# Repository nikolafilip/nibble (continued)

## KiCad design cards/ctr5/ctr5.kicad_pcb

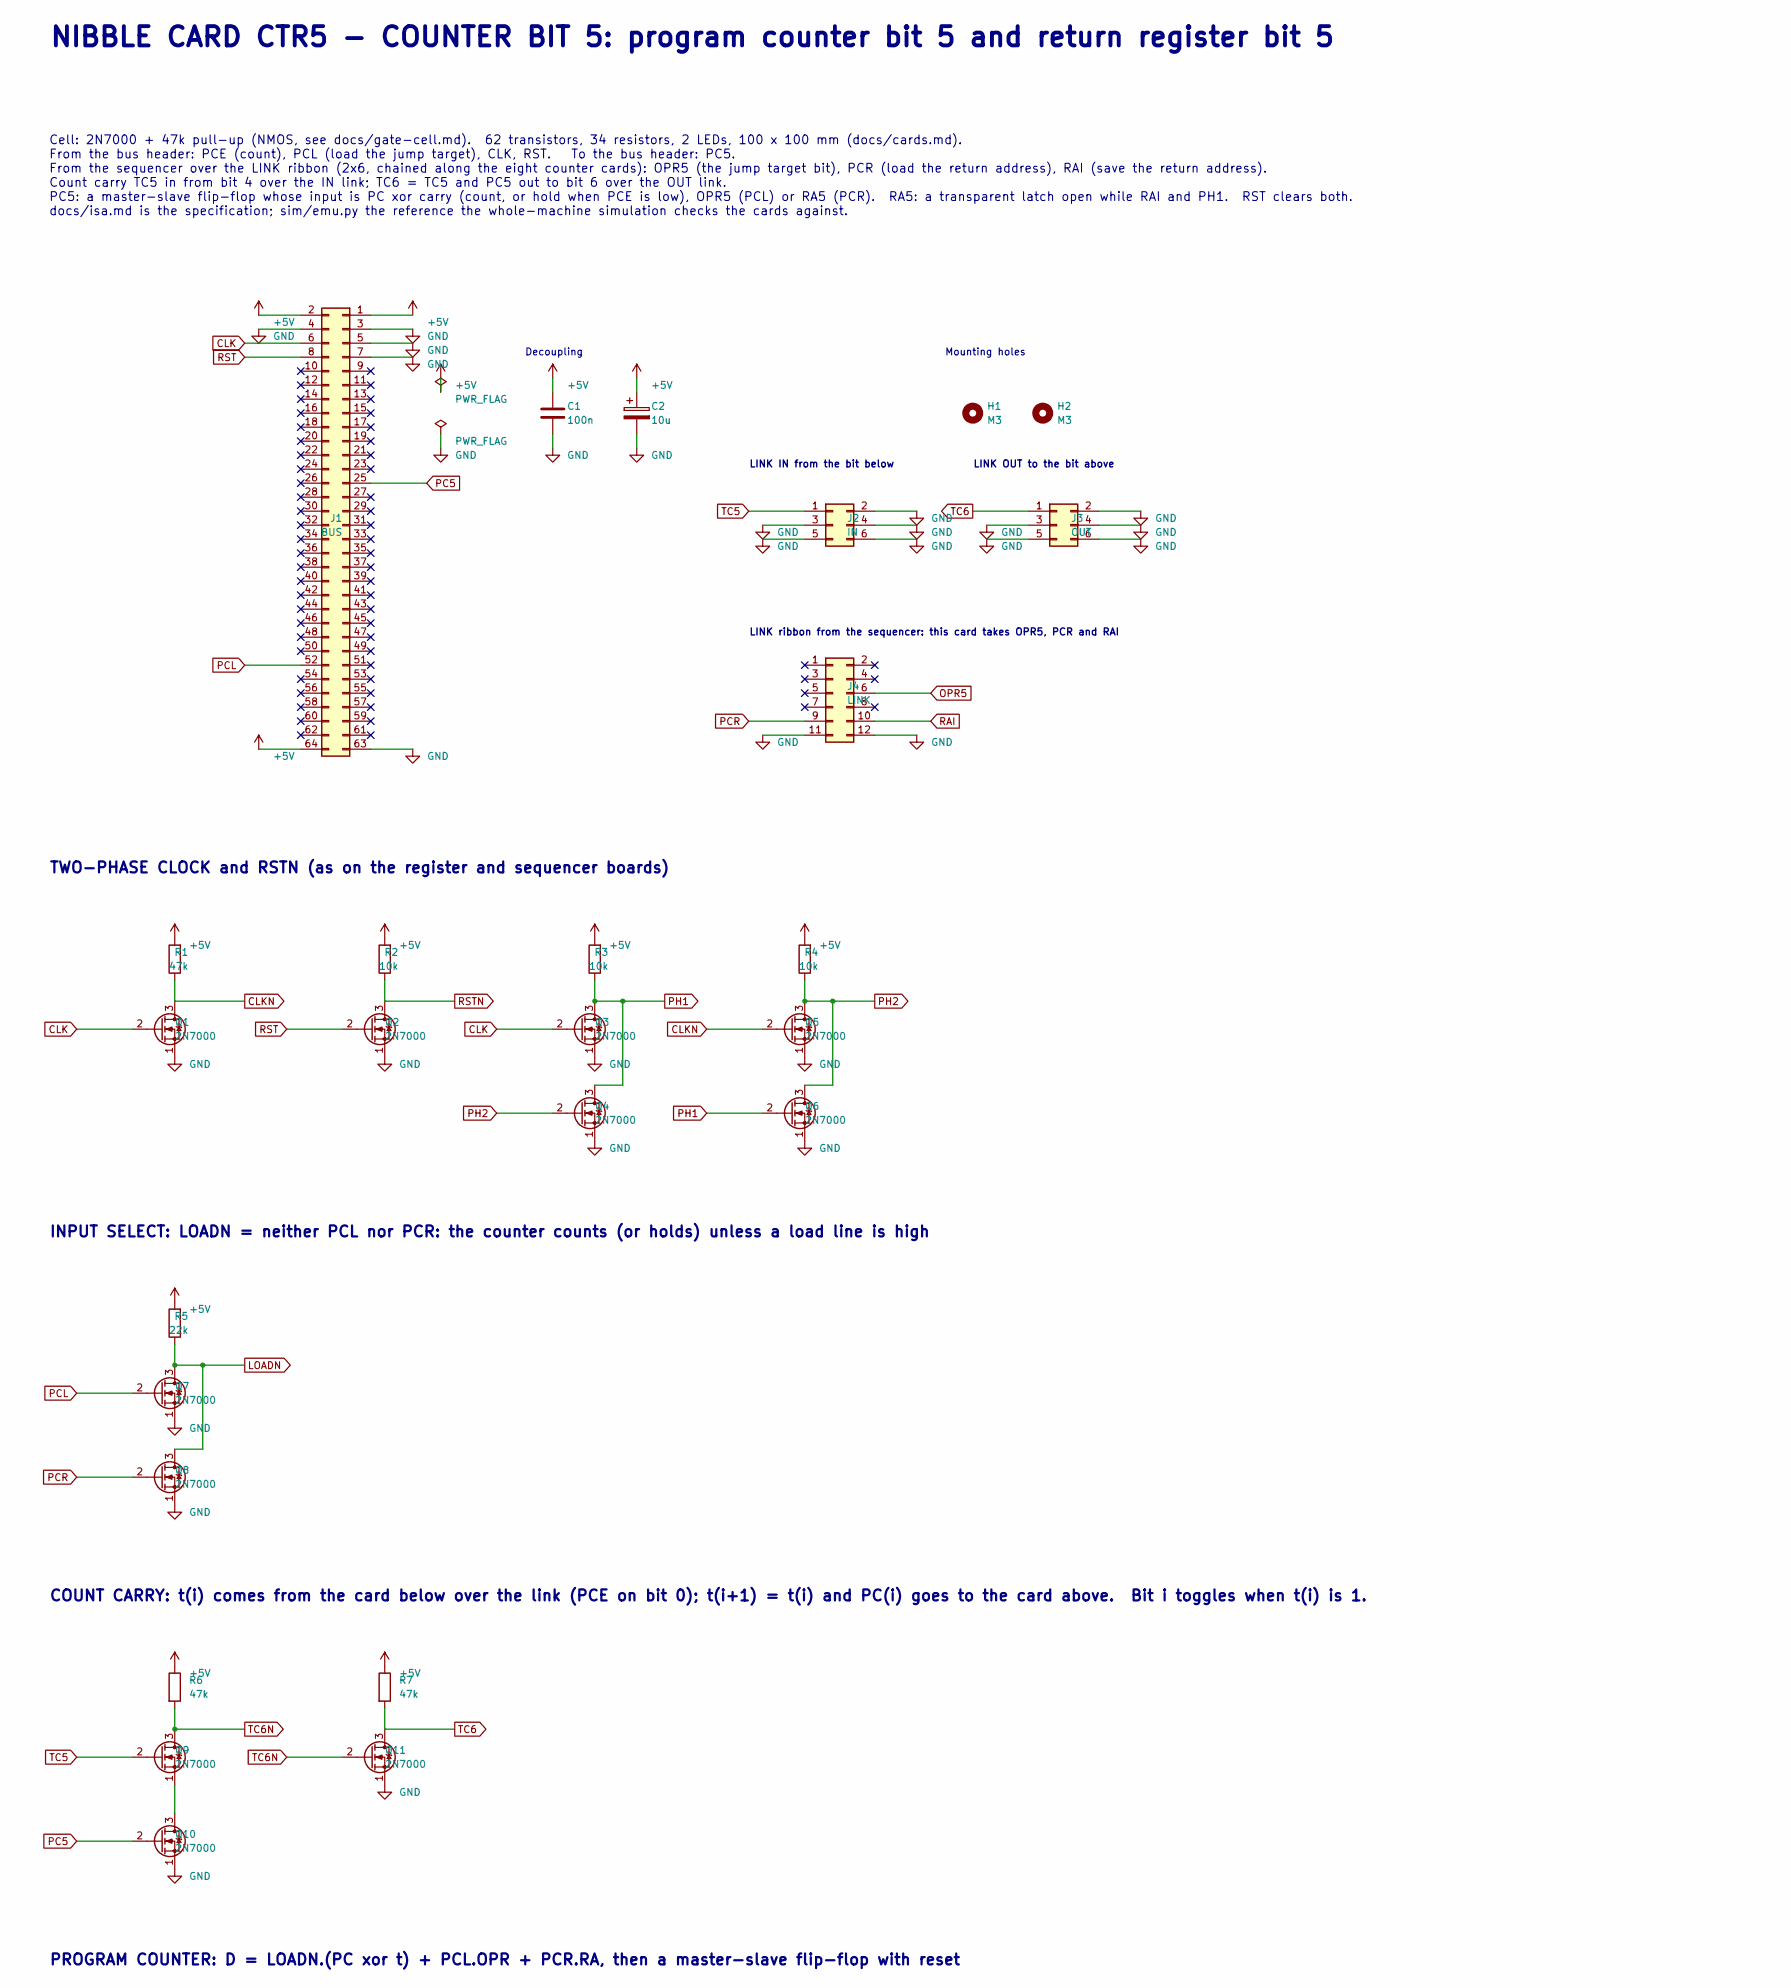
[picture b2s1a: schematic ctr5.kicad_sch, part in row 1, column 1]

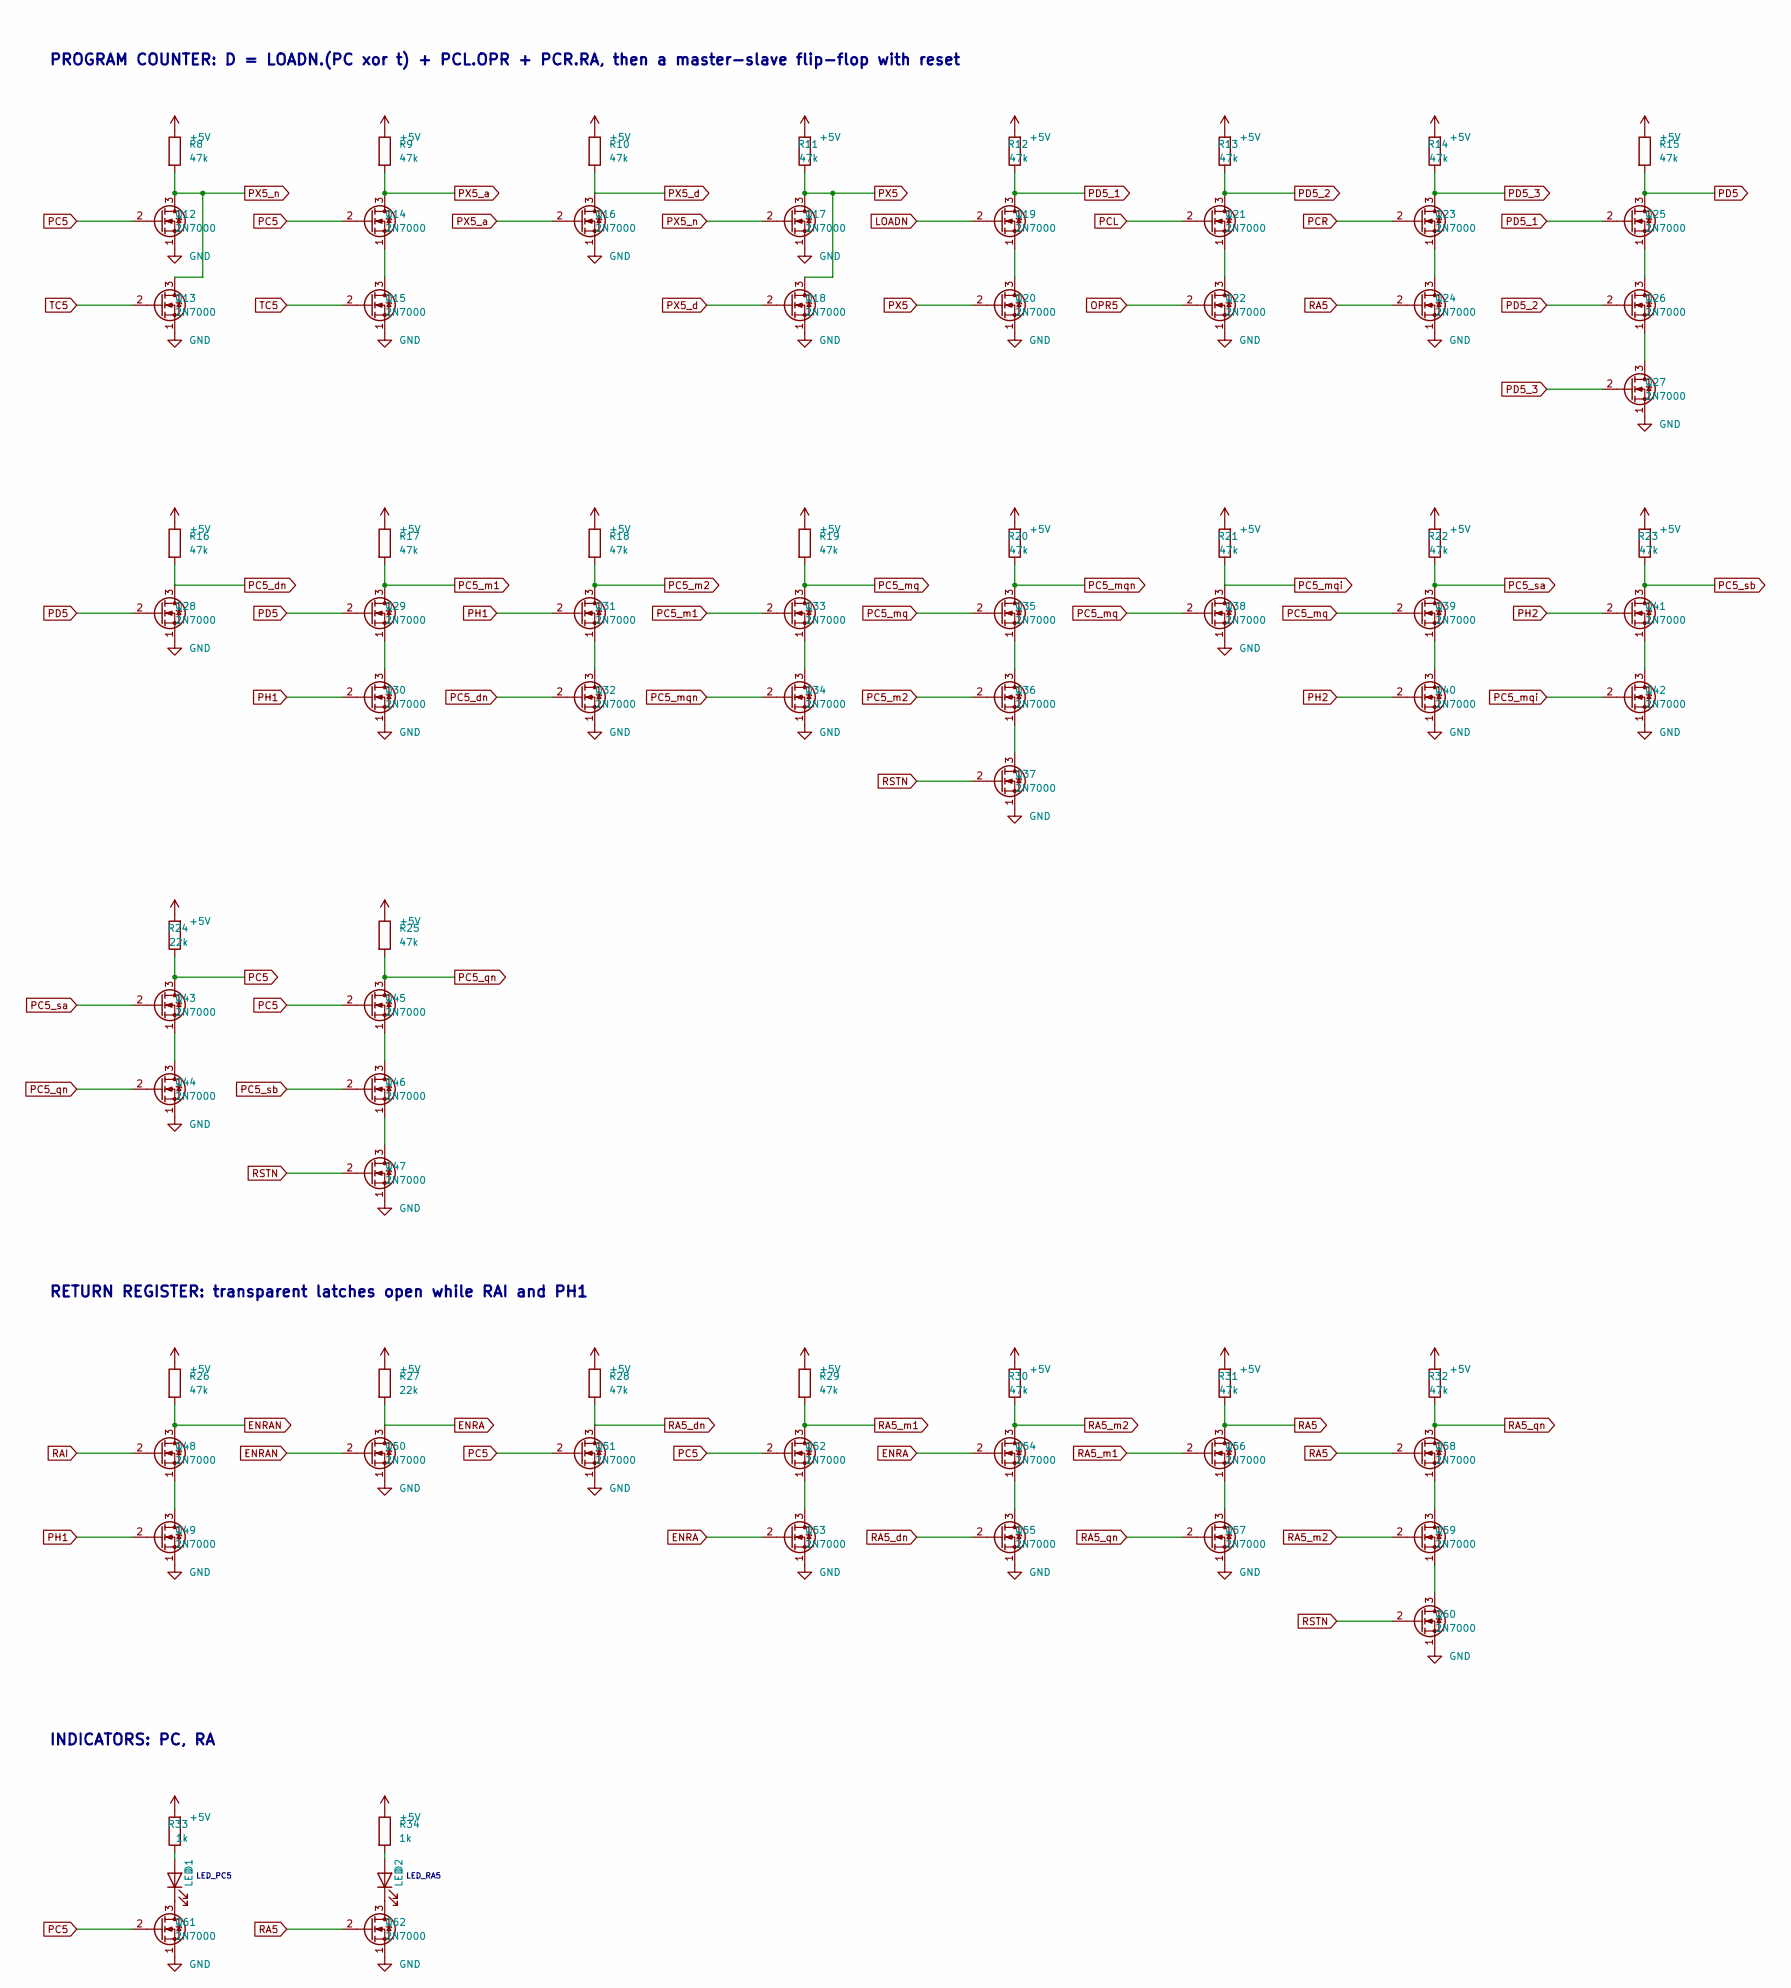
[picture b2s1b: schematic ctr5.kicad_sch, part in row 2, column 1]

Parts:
C1: 100n; C_Disc_D5.0mm_W2.5mm_P2.50mm
C2: 10u; CP_Radial_D5.0mm_P2.00mm
D1, D2: LED; LED_D3.0mm
H1, H2: M3; MountingHole_3.2mm_M3_Pad
J1: BUS; IDC-Header_2x32_P2.54mm_Vertical
J2: IN; IDC-Header_2x03_P2.54mm_Vertical
J3: OUT; IDC-Header_2x03_P2.54mm_Vertical
J4: LINK; IDC-Header_2x06_P2.54mm_Vertical
Q1, Q2, Q3, Q4, Q5, Q6, Q7, Q8, Q9, Q10, Q11, Q12, Q13, Q14, Q15, Q16, Q17, Q18, Q19, Q20, Q21, Q22, Q23, Q24, Q25, Q26, Q27, Q28, Q29, Q30, Q31, Q32, Q33, Q34, Q35, Q36, Q37, Q38, Q39, Q40, Q41, Q42, Q43, Q44, Q45, Q46, Q47, Q48, Q49, Q50, Q51, Q52, Q53, Q54, Q55, Q56, Q57, Q58, Q59, Q60, Q61, Q62: 2N7000; TO-92_Inline_Wide
R1, R6, R7, R8, R9, R10, R11, R12, R13, R14, R15, R16, R17, R18, R19, R20, R21, R22, R23, R25, R26, R28, R29, R30, R31, R32: 47k; R_Axial_DIN0207_L6.3mm_D2.5mm_P5.08mm_Vertical
R2, R3, R4: 10k; R_Axial_DIN0207_L6.3mm_D2.5mm_P5.08mm_Vertical
R5, R24, R27: 22k; R_Axial_DIN0207_L6.3mm_D2.5mm_P5.08mm_Vertical
R33, R34: 1k; R_Axial_DIN0207_L6.3mm_D2.5mm_P5.08mm_Vertical

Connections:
+5V: C1.1, C2.1, J1.1, J1.2, J1.64, R1.2, R2.2, R3.2, R4.2, R5.2, R6.1, R7.1, R8.1, R9.1, R10.1, R11.2, R12.2, R13.2, R14.2, R15.1, R16.1, R17.1, R18.1, R19.1, R20.2, R21.2, R22.2, R23.2, R24.2, R25.1, R26.1, R27.1, R28.1, R29.1, R30.2, R31.2, R32.2, R33.2, R34.1
CLK: J1.6, Q1.2 (G), Q3.2 (G)
CLKN: Q1.3 (D), Q5.2 (G), R1.1
ENRA: Q50.3 (D), Q53.2 (G), Q54.2 (G), R27.2
ENRAN: Q48.3 (D), Q50.2 (G), R26.2
GND: C1.2, C2.2, J1.3, J1.4, J1.5, J1.7, J1.63, J2.2, J2.3, J2.4, J2.5, J2.6, J3.2, J3.3, J3.4, J3.5, J3.6, J4.11, J4.12, Q1.1 (S), Q2.1 (S), Q3.1 (S), Q4.1 (S), Q5.1 (S), Q6.1 (S), Q7.1 (S), Q8.1 (S), Q10.1 (S), Q11.1 (S), Q12.1 (S), Q13.1 (S), Q15.1 (S), Q16.1 (S), Q17.1 (S), Q18.1 (S), Q20.1 (S), Q22.1 (S), Q24.1 (S), Q27.1 (S), Q28.1 (S), Q30.1 (S), Q32.1 (S), Q34.1 (S), Q37.1 (S), Q38.1 (S), Q40.1 (S), Q42.1 (S), Q44.1 (S), Q47.1 (S), Q49.1 (S), Q50.1 (S), Q51.1 (S), Q53.1 (S), Q55.1 (S), Q57.1 (S), Q60.1 (S), Q61.1 (S), Q62.1 (S)
LOADN: Q7.3 (D), Q8.3 (D), Q19.2 (G), R5.1
unnamed: D1.2 (A), R33.1
unnamed: D1.1 (K), Q61.3 (D)
unnamed: D2.2 (A), R34.2
unnamed: D2.1 (K), Q62.3 (D)
unnamed: Q9.1 (S), Q10.3 (D)
unnamed: Q14.1 (S), Q15.3 (D)
unnamed: Q19.1 (S), Q20.3 (D)
unnamed: Q21.1 (S), Q22.3 (D)
unnamed: Q23.1 (S), Q24.3 (D)
unnamed: Q25.1 (S), Q26.3 (D)
unnamed: Q26.1 (S), Q27.3 (D)
unnamed: Q29.1 (S), Q30.3 (D)
unnamed: Q31.1 (S), Q32.3 (D)
unnamed: Q33.1 (S), Q34.3 (D)
unnamed: Q35.1 (S), Q36.3 (D)
unnamed: Q36.1 (S), Q37.3 (D)
unnamed: Q39.1 (S), Q40.3 (D)
unnamed: Q41.1 (S), Q42.3 (D)
unnamed: Q43.1 (S), Q44.3 (D)
unnamed: Q45.1 (S), Q46.3 (D)
unnamed: Q46.1 (S), Q47.3 (D)
unnamed: Q48.1 (S), Q49.3 (D)
unnamed: Q52.1 (S), Q53.3 (D)
unnamed: Q54.1 (S), Q55.3 (D)
unnamed: Q56.1 (S), Q57.3 (D)
unnamed: Q58.1 (S), Q59.3 (D)
unnamed: Q59.1 (S), Q60.3 (D)
OPR5: J4.6, Q22.2 (G)
PC5: J1.25, Q10.2 (G), Q12.2 (G), Q14.2 (G), Q43.3 (D), Q45.2 (G), Q51.2 (G), Q52.2 (G), Q61.2 (G), R24.1
PC5_dn: Q28.3 (D), Q32.2 (G), R16.2
PC5_m1: Q29.3 (D), Q33.2 (G), R17.2
PC5_m2: Q31.3 (D), Q36.2 (G), R18.2
PC5_mq: Q33.3 (D), Q35.2 (G), Q38.2 (G), Q39.2 (G), R19.2
PC5_mqi: Q38.3 (D), Q42.2 (G), R21.1
PC5_mqn: Q34.2 (G), Q35.3 (D), R20.1
PC5_qn: Q44.2 (G), Q45.3 (D), R25.2
PC5_sa: Q39.3 (D), Q43.2 (G), R22.1
PC5_sb: Q41.3 (D), Q46.2 (G), R23.1
PCL: J1.52, Q7.2 (G), Q21.2 (G)
PCR: J4.9, Q8.2 (G), Q23.2 (G)
PD5: Q25.3 (D), Q28.2 (G), Q29.2 (G), R15.2
PD5_1: Q19.3 (D), Q25.2 (G), R12.1
PD5_2: Q21.3 (D), Q26.2 (G), R13.1
PD5_3: Q23.3 (D), Q27.2 (G), R14.1
PH1: Q3.3 (D), Q4.3 (D), Q6.2 (G), Q30.2 (G), Q31.2 (G), Q49.2 (G), R3.1
PH2: Q4.2 (G), Q5.3 (D), Q6.3 (D), Q40.2 (G), Q41.2 (G), R4.1
PX5: Q17.3 (D), Q18.3 (D), Q20.2 (G), R11.1
PX5_a: Q14.3 (D), Q16.2 (G), R9.2
PX5_d: Q16.3 (D), Q18.2 (G), R10.2
PX5_n: Q12.3 (D), Q13.3 (D), Q17.2 (G), R8.2
RA5: Q24.2 (G), Q56.3 (D), Q58.2 (G), Q62.2 (G), R31.1
RA5_dn: Q51.3 (D), Q55.2 (G), R28.2
RA5_m1: Q52.3 (D), Q56.2 (G), R29.2
RA5_m2: Q54.3 (D), Q59.2 (G), R30.1
RA5_qn: Q57.2 (G), Q58.3 (D), R32.1
RAI: J4.10, Q48.2 (G)
RST: J1.8, Q2.2 (G)
RSTN: Q2.3 (D), Q37.2 (G), Q47.2 (G), Q60.2 (G), R2.1
TC5: J2.1, Q9.2 (G), Q13.2 (G), Q15.2 (G)
TC6: J3.1, Q11.3 (D), R7.2
TC6N: Q9.3 (D), Q11.2 (G), R6.2

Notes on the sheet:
NIBBLE CARD CTR5 - COUNTER BIT 5: program counter bit 5 and return register bit 5
Cell: 2N7000 + 47k pull-up (NMOS, see docs/gate-cell.md). 62 transistors, 34 resistors, 2 LEDs, 100 x 100 mm (docs/cards.md). From the bus header: PCE (count), PCL (load the jump target), CLK, RST. To the bus header: PC5. From the sequencer over the LINK ribbon (2x6, chained along the eight counter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
TWO-PHASE CLOCK and RSTN (as on the register and sequencer boards)
INPUT SELECT: LOADN = neither PCL nor PCR: the counter counts (or holds) unless a load line is high
COUNT CARRY: t(i) comes from the card below over the link (PCE on bit 0); t(i+1) = t(i) and PC(i) goes to the card above. Bit i toggles when t(i) is 1.
PROGRAM COUNTER: D = LOADN.(PC xor t) + PCL.OPR + PCR.RA, then a master-slave flip-flop with reset
RETURN REGISTER: transparent latches open while RAI and PH1
INDICATORS: PC, RA
LED_PC5
LED_RA5
Decoupling
Mounting holes
LINK IN from the bit below
LINK OUT to the bit above
LINK ribbon from the sequencer: this card takes OPR5, PCR and RAI

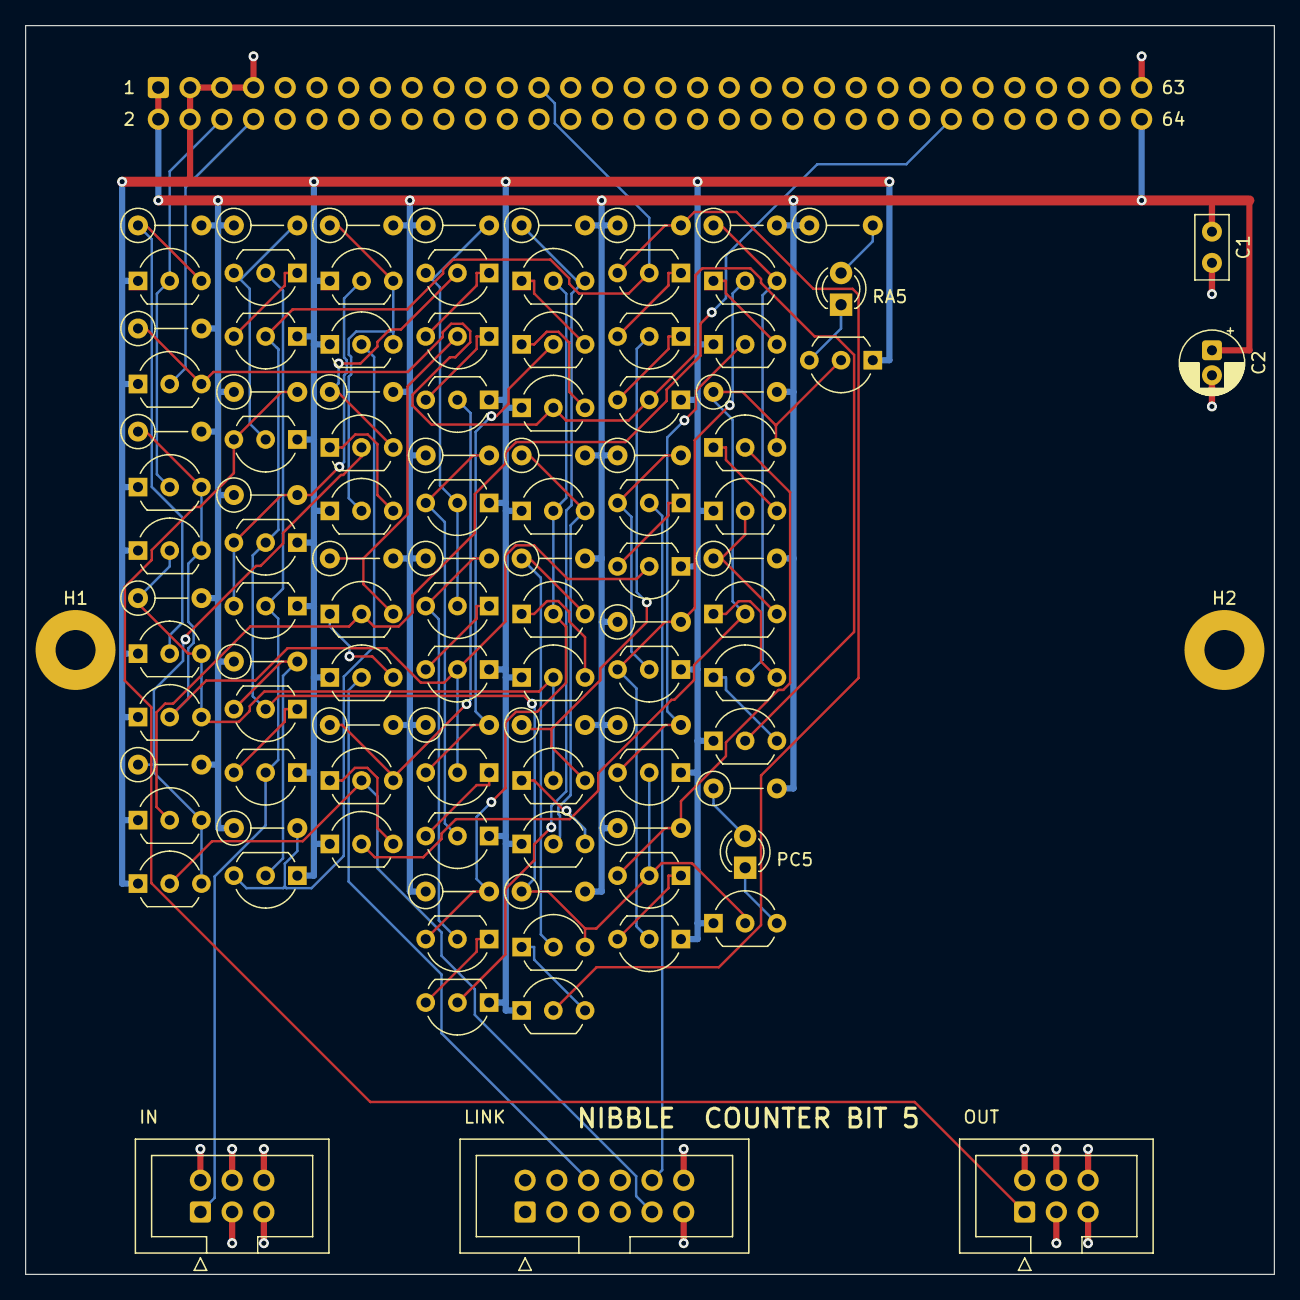
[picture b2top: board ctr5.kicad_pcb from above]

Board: 2 copper layers, 100.0 x 100.0 mm, 106 parts (1 on the bottom side), 68 nets.

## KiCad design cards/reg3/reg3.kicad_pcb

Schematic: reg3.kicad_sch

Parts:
C1: 100n; C_Disc_D5.0mm_W2.5mm_P2.50mm
C2: 10u; CP_Radial_D5.0mm_P2.00mm
D1, D2, D3: LED; LED_D3.0mm
H1, H2: M3; MountingHole_3.2mm_M3_Pad
J1: BUS; IDC-Header_2x32_P2.54mm_Vertical
Q1, Q2, Q3, Q4, Q5, Q6, Q7, Q8, Q9, Q10, Q11, Q12, Q13, Q14, Q15, Q16, Q17, Q18, Q19, Q20, Q21, Q22, Q23, Q24, Q25, Q26, Q27, Q28, Q29, Q30, Q31, Q32, Q33, Q34, Q35, Q36, Q37, Q38, Q39, Q40, Q41, Q42, Q43, Q44, Q45, Q46, Q47, Q48, Q49, Q50, Q51, Q52, Q53, Q54, Q55, Q56, Q57, Q58, Q59, Q60, Q61, Q62, Q63, Q64, Q65, Q66, Q67, Q68, Q69, Q70, Q71, Q72, Q73, Q74, Q75, Q76, Q77, Q78, Q79, Q80, Q81, Q82, Q83, Q84, Q85, Q86, Q87, Q88, Q89, Q90, Q91, Q92, Q93, Q94, Q95, Q96, Q97, Q98, Q99: 2N7000; TO-92_Inline_Wide
R1, R4, R5, R6, R7, R8, R9, R10, R11, R12, R13, R14, R15, R16, R17, R19, R20, R21, R22, R23, R24, R25, R26, R27, R28, R29, R30, R31, R32, R34, R35, R36, R37, R38, R39, R40, R41, R42, R43, R44, R45, R46, R47, R48, R49, R50, R51: 47k; R_Axial_DIN0207_L6.3mm_D2.5mm_P5.08mm_Vertical
R2, R3: 10k; R_Axial_DIN0207_L6.3mm_D2.5mm_P5.08mm_Vertical
R18, R33: 22k; R_Axial_DIN0207_L6.3mm_D2.5mm_P5.08mm_Vertical
R52, R53, R54: 1k; R_Axial_DIN0207_L6.3mm_D2.5mm_P5.08mm_Vertical

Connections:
+5V: C1.1, C2.1, J1.1, J1.2, J1.64, R1.2, R2.2, R3.2, R4.2, R5.2, R6.2, R7.1, R8.1, R9.1, R10.1, R11.1, R12.1, R13.2, R14.2, R15.2, R16.2, R17.2, R18.2, R19.1, R20.1, R21.1, R22.1, R23.1, R24.2, R25.2, R26.2, R27.2, R28.2, R29.2, R30.1, R31.1, R32.1, R33.1, R34.1, R35.1, R36.2, R37.2, R38.2, R39.2, R40.2, R41.2, R42.1, R43.1, R44.1, R45.1, R46.1, R47.1, R48.2, R49.2, R50.2, R51.2, R52.2, R53.1, R54.1
A3: J1.15, Q14.2 (G), Q32.3 (D), Q34.2 (G), Q41.2 (G), Q91.2 (G), Q98.2 (G), R18.1
A3_dn: Q18.3 (D), Q22.2 (G), R10.2
A3_m1: Q19.3 (D), Q23.2 (G), R11.2
A3_m2: Q21.3 (D), Q26.2 (G), R12.2
A3_mq: Q23.3 (D), Q25.2 (G), Q27.2 (G), Q28.2 (G), R13.1
A3_mqi: Q27.3 (D), Q31.2 (G), R15.1
A3_mqn: Q24.2 (G), Q25.3 (D), R14.1
A3_qn: Q33.2 (G), Q34.3 (D), R19.2
A3_sa: Q28.3 (D), Q32.2 (G), R16.1
A3_sb: Q30.3 (D), Q35.2 (G), R17.1
AB: J1.45, Q8.2 (G), Q11.2 (G)
AI: J1.42, Q7.2 (G), Q9.2 (G)
AO: J1.41, Q90.2 (G)
AON3: Q90.3 (D), Q94.2 (G), R49.1
B3: J1.19, Q12.2 (G), Q43.2 (G), Q61.3 (D), Q63.2 (G), Q93.2 (G), Q99.2 (G), R33.2
B3_dn: Q47.3 (D), Q51.2 (G), R25.1
B3_m1: Q48.3 (D), Q52.2 (G), R26.1
B3_m2: Q50.3 (D), Q55.2 (G), R27.1
B3_mq: Q52.3 (D), Q54.2 (G), Q56.2 (G), Q57.2 (G), R28.1
B3_mqi: Q56.3 (D), Q60.2 (G), R30.2
B3_mqn: Q53.2 (G), Q54.3 (D), R29.1
B3_qn: Q62.2 (G), Q63.3 (D), R34.2
B3_sa: Q57.3 (D), Q61.2 (G), R31.2
B3_sb: Q59.3 (D), Q64.2 (G), R32.2
BA: J1.46, Q37.2 (G), Q40.2 (G)
BD3: Q94.3 (D), Q96.2 (G), R51.1
BI: J1.44, Q36.2 (G), Q38.2 (G)
BO: J1.43, Q92.2 (G)
BON3: Q92.3 (D), Q95.2 (G), R50.1
BUS3#: J1.11, Q6.2 (G), Q96.3 (D)
CLK: J1.6, Q1.2 (G), Q2.2 (G)
CLKN: Q1.3 (D), Q4.2 (G), R1.1
D3: Q6.3 (D), Q10.2 (G), Q39.2 (G), Q67.2 (G), R4.1
DA3: Q15.3 (D), Q18.2 (G), Q19.2 (G), R9.2
DA3_1: Q9.3 (D), Q15.2 (G), R6.1
DA3_2: Q11.3 (D), Q16.2 (G), R7.2
DA3_3: Q13.3 (D), Q17.2 (G), R8.2
DB3: Q44.3 (D), Q47.2 (G), Q48.2 (G), R24.1
DB3_1: Q38.3 (D), Q44.2 (G), R21.2
DB3_2: Q40.3 (D), Q45.2 (G), R22.2
DB3_3: Q42.3 (D), Q46.2 (G), R23.2
DO3: Q70.3 (D), Q72.2 (G), Q73.2 (G), R38.1
DO3_1: Q66.3 (D), Q70.2 (G), R36.1
DO3_2: Q68.3 (D), Q71.2 (G), R37.1
GND: C1.2, C2.2, J1.3, J1.4, J1.5, J1.7, J1.63, Q1.1 (S), Q2.1 (S), Q3.1 (S), Q4.1 (S), Q5.1 (S), Q6.1 (S), Q7.1 (S), Q8.1 (S), Q10.1 (S), Q12.1 (S), Q14.1 (S), Q17.1 (S), Q18.1 (S), Q20.1 (S), Q22.1 (S), Q24.1 (S), Q26.1 (S), Q27.1 (S), Q29.1 (S), Q31.1 (S), Q33.1 (S), Q35.1 (S), Q36.1 (S), Q37.1 (S), Q39.1 (S), Q41.1 (S), Q43.1 (S), Q46.1 (S), Q47.1 (S), Q49.1 (S), Q51.1 (S), Q53.1 (S), Q55.1 (S), Q56.1 (S), Q58.1 (S), Q60.1 (S), Q62.1 (S), Q64.1 (S), Q65.1 (S), Q67.1 (S), Q69.1 (S), Q71.1 (S), Q72.1 (S), Q74.1 (S), Q76.1 (S), Q78.1 (S), Q80.1 (S), Q81.1 (S), Q83.1 (S), Q85.1 (S), Q87.1 (S), Q89.1 (S), Q91.1 (S), Q93.1 (S), Q95.1 (S), Q96.1 (S), Q97.1 (S), Q98.1 (S), Q99.1 (S)
HOLDA: Q7.3 (D), Q8.3 (D), Q13.2 (G), R5.1
HOLDB: Q36.3 (D), Q37.3 (D), Q42.2 (G), R20.2
unnamed: D1.2 (A), R52.1
unnamed: D1.1 (K), Q97.3 (D)
unnamed: D2.2 (A), R53.2
unnamed: D2.1 (K), Q98.3 (D)
unnamed: D3.2 (A), R54.2
unnamed: D3.1 (K), Q99.3 (D)
unnamed: Q9.1 (S), Q10.3 (D)
unnamed: Q11.1 (S), Q12.3 (D)
unnamed: Q13.1 (S), Q14.3 (D)
unnamed: Q15.1 (S), Q16.3 (D)
unnamed: Q16.1 (S), Q17.3 (D)
unnamed: Q19.1 (S), Q20.3 (D)
unnamed: Q21.1 (S), Q22.3 (D)
unnamed: Q23.1 (S), Q24.3 (D)
unnamed: Q25.1 (S), Q26.3 (D)
unnamed: Q28.1 (S), Q29.3 (D)
unnamed: Q30.1 (S), Q31.3 (D)
unnamed: Q32.1 (S), Q33.3 (D)
unnamed: Q34.1 (S), Q35.3 (D)
unnamed: Q38.1 (S), Q39.3 (D)
unnamed: Q40.1 (S), Q41.3 (D)
unnamed: Q42.1 (S), Q43.3 (D)
unnamed: Q44.1 (S), Q45.3 (D)
unnamed: Q45.1 (S), Q46.3 (D)
unnamed: Q48.1 (S), Q49.3 (D)
unnamed: Q50.1 (S), Q51.3 (D)
unnamed: Q52.1 (S), Q53.3 (D)
unnamed: Q54.1 (S), Q55.3 (D)
unnamed: Q57.1 (S), Q58.3 (D)
unnamed: Q59.1 (S), Q60.3 (D)
unnamed: Q61.1 (S), Q62.3 (D)
unnamed: Q63.1 (S), Q64.3 (D)
unnamed: Q66.1 (S), Q67.3 (D)
unnamed: Q68.1 (S), Q69.3 (D)
unnamed: Q70.1 (S), Q71.3 (D)
unnamed: Q73.1 (S), Q74.3 (D)
unnamed: Q75.1 (S), Q76.3 (D)
unnamed: Q77.1 (S), Q78.3 (D)
unnamed: Q79.1 (S), Q80.3 (D)
unnamed: Q82.1 (S), Q83.3 (D)
unnamed: Q84.1 (S), Q85.3 (D)
unnamed: Q86.1 (S), Q87.3 (D)
unnamed: Q88.1 (S), Q89.3 (D)
unnamed: Q90.1 (S), Q91.3 (D)
unnamed: Q92.1 (S), Q93.3 (D)
unnamed: Q94.1 (S), Q95.3 (D)
OI: J1.48, Q65.2 (G), Q66.2 (G)
OIN: Q65.3 (D), Q68.2 (G), R35.2
OUT3: Q69.2 (G), Q86.3 (D), Q88.2 (G), Q97.2 (G), R47.2
OUT3_dn: Q72.3 (D), Q76.2 (G), R39.1
OUT3_m1: Q73.3 (D), Q77.2 (G), R40.1
OUT3_m2: Q75.3 (D), Q80.2 (G), R41.1
OUT3_mq: Q77.3 (D), Q79.2 (G), Q81.2 (G), Q82.2 (G), R42.2
OUT3_mqi: Q81.3 (D), Q85.2 (G), R44.2
OUT3_mqn: Q78.2 (G), Q79.3 (D), R43.2
OUT3_qn: Q87.2 (G), Q88.3 (D), R48.1
OUT3_sa: Q82.3 (D), Q86.2 (G), R45.2
OUT3_sb: Q84.3 (D), Q89.2 (G), R46.2
PH1: Q2.3 (D), Q3.3 (D), Q5.2 (G), Q20.2 (G), Q21.2 (G), Q49.2 (G), Q50.2 (G), Q74.2 (G), Q75.2 (G), R2.1
PH2: Q3.2 (G), Q4.3 (D), Q5.3 (D), Q29.2 (G), Q30.2 (G), Q58.2 (G), Q59.2 (G), Q83.2 (G), Q84.2 (G), R3.1

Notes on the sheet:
NIBBLE CARD REG3 - REGISTER BIT 3: bit 3 of A, B and OUT
Cell: 2N7000 + 47k pull-up (NMOS, see docs/gate-cell.md). 99 transistors, 54 resistors, 3 LEDs, 100 x 100 mm (docs/cards.md). From the bus header: BUS3# (data, active low), CLK, and the control lines AI AO BI BO BA AB OI (docs/isa.md). To the bus header: A3 and B3 (for the ALU and the panel); BUS3#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
TWO-PHASE CLOCK (one per card): PH1 = NOR(CLK, PH2) opens the masters while CLK is low, PH2 = NOR(CLKN, PH1) opens the slaves while CLK is high. The cross-coupling means a phase cannot start rising until the other is fully low, so a flip-flop is never transparent.
BUS INPUT: D = NOT BUS# (the bus is active low)
REGISTER A INPUT MUX: DA = AI.D + AB.B + HOLDA.A, HOLDA = NOR(AI, AB). NAND-NAND form: three 2-input NANDs into a 3-input NAND
REGISTER A: master-slave D flip-flop, 22k pull-up on Q (A feeds the ALU, the panel, both muxes and the bus driver)
REGISTER B INPUT MUX: DB = BI.D + BA.A + HOLDB.B
REGISTER B
OUT REGISTER INPUT MUX: DO = OI.D + OIN.OUT
OUT REGISTER (the display)
BUS DRIVER: pull BUS# low when AO.A or BO.B
INDICATORS: OUT, A, B
LED_OUT3
LED_A3
LED_B3
Decoupling
Mounting holes

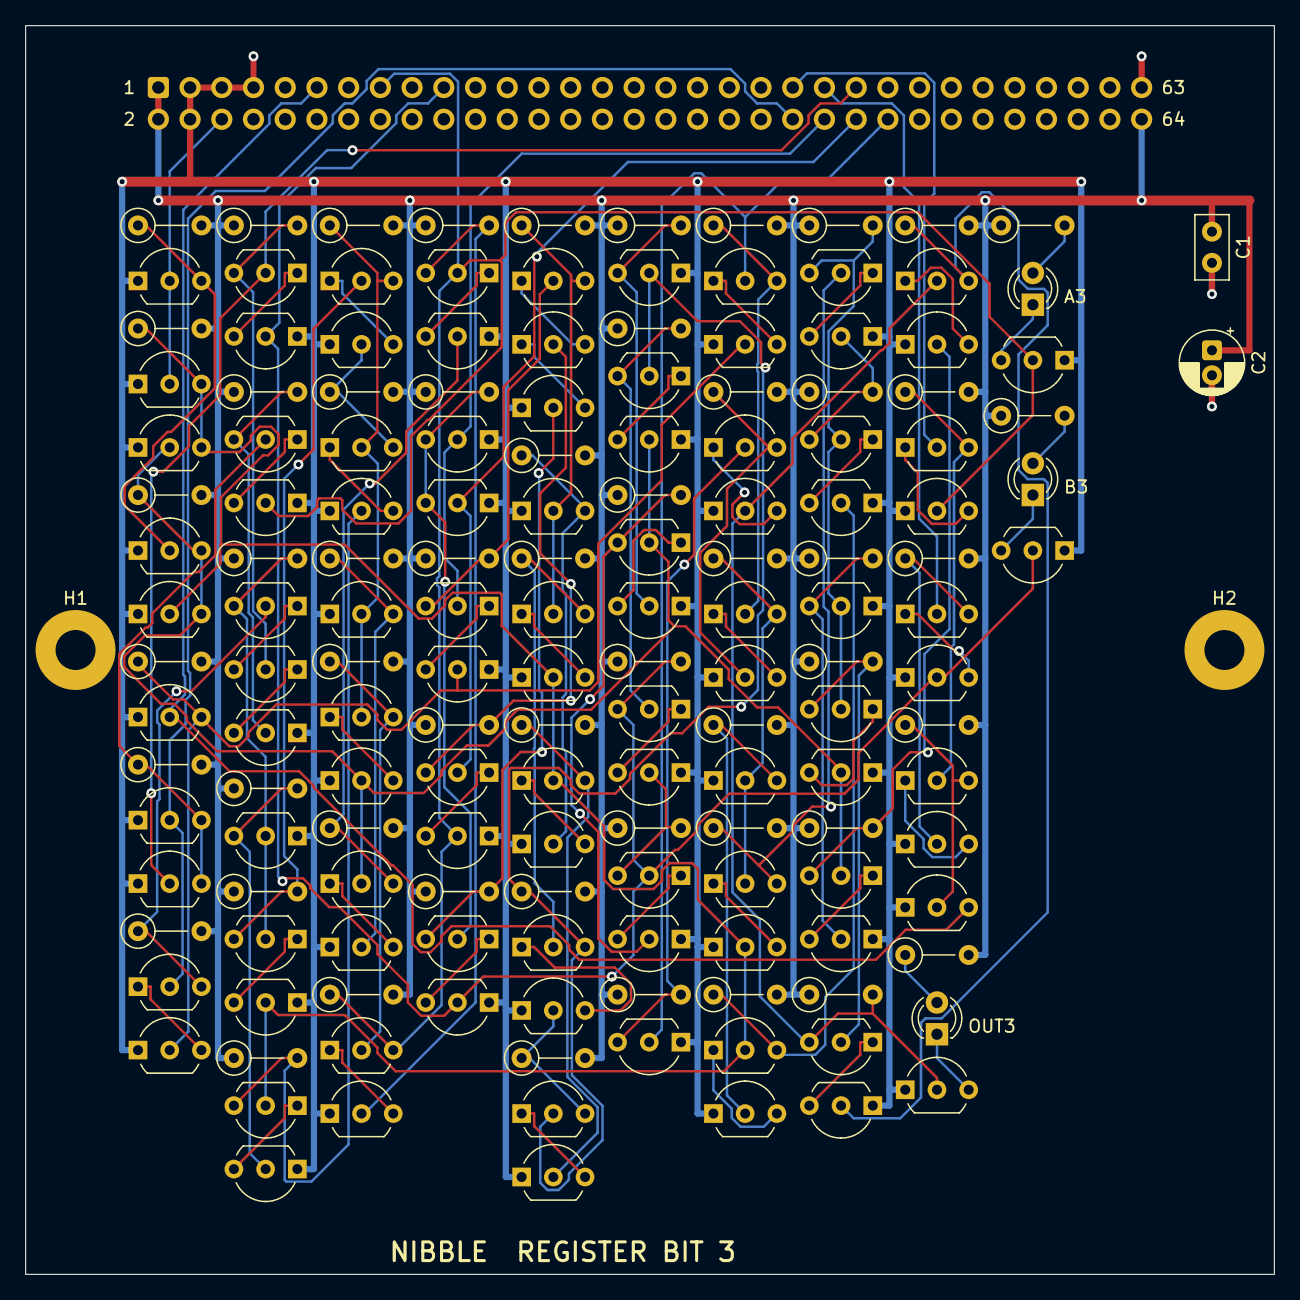
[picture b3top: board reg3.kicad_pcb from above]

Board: 2 copper layers, 100.0 x 100.0 mm, 161 parts (1 on the bottom side), 108 nets.
